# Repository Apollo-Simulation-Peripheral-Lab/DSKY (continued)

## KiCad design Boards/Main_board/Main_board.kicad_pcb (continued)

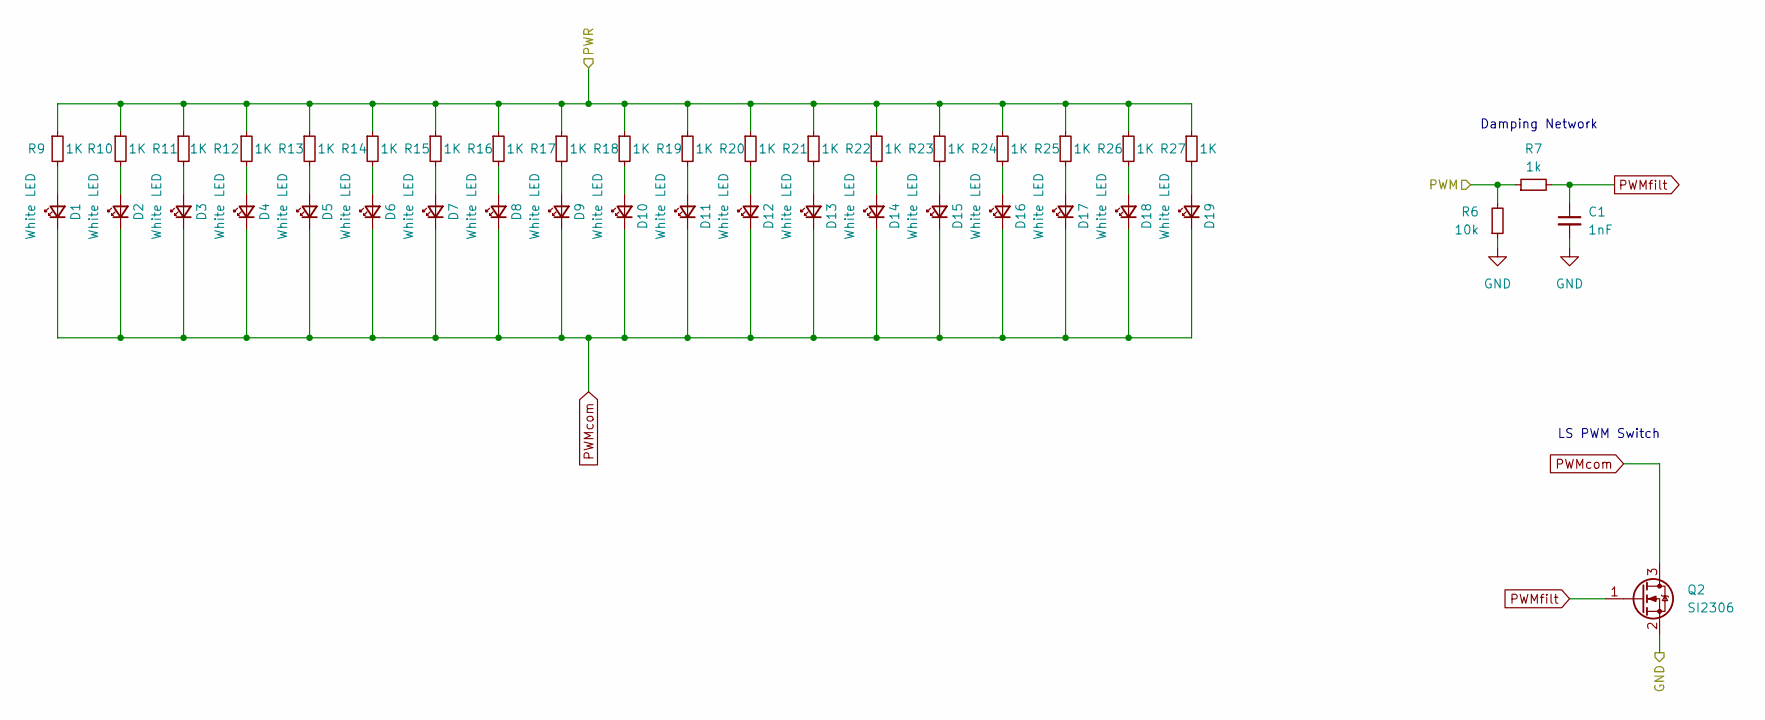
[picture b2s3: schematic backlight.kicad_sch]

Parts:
C1: 1nF; C_1206_3216Metric_Pad1.33x1.80mm_HandSolder; Part Number C1206C102K5RAC
D1, D2, D3, D4, D5, D6, D7, D8, D9, D10, D11, D12, D13, D14, D15, D16, D17, D18, D19: White LED; MX-LED-PolarityMarked
Q2: SI2306; SOT-23-3; Part Number SI2306-TP
R6: 10k; R_1206_3216Metric; Part Number CR1206-FX-1002ELF
R7: 1k; R_1206_3216Metric; Part Number CR1206-FX-1001ELF
R9, R10, R11, R12, R13, R14, R15, R16, R17, R18, R19, R20, R21, R22, R23, R24, R25, R26, R27: 1K; R_1206_3216Metric

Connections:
+5V: R9.1, R10.1, R11.1, R12.1, R13.1, R14.1, R15.1, R16.1, R17.1, R18.1, R19.1, R20.1, R21.1, R22.1, R23.1, R24.1, R25.1, R26.1, R27.1; also elsewhere on the board
GND: C1.2, Q2.2 (S), R6.1; also elsewhere on the board
unnamed: D1.2 (A), R9.2
unnamed: D2.2 (A), R10.2
unnamed: D3.2 (A), R11.2
unnamed: D4.2 (A), R12.2
unnamed: D5.2 (A), R13.2
unnamed: D6.2 (A), R14.2
unnamed: D7.2 (A), R15.2
unnamed: D8.2 (A), R16.2
unnamed: D9.2 (A), R17.2
unnamed: D10.2 (A), R18.2
unnamed: D11.2 (A), R19.2
unnamed: D12.2 (A), R20.2
unnamed: D13.2 (A), R21.2
unnamed: D14.2 (A), R22.2
unnamed: D15.2 (A), R23.2
unnamed: D16.2 (A), R24.2
unnamed: D17.2 (A), R25.2
unnamed: D18.2 (A), R26.2
unnamed: D19.2 (A), R27.2
PWM: R6.2, R7.1; also elsewhere on the board
PWMcom: D1.1 (K), D2.1 (K), D3.1 (K), D4.1 (K), D5.1 (K), D6.1 (K), D7.1 (K), D8.1 (K), D9.1 (K), D10.1 (K), D11.1 (K), D12.1 (K), D13.1 (K), D14.1 (K), D15.1 (K), D16.1 (K), D17.1 (K), D18.1 (K), D19.1 (K), Q2.3 (D)
PWMfilt: C1.1, Q2.1 (G), R7.2

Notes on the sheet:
LS PWM Switch
Damping Network

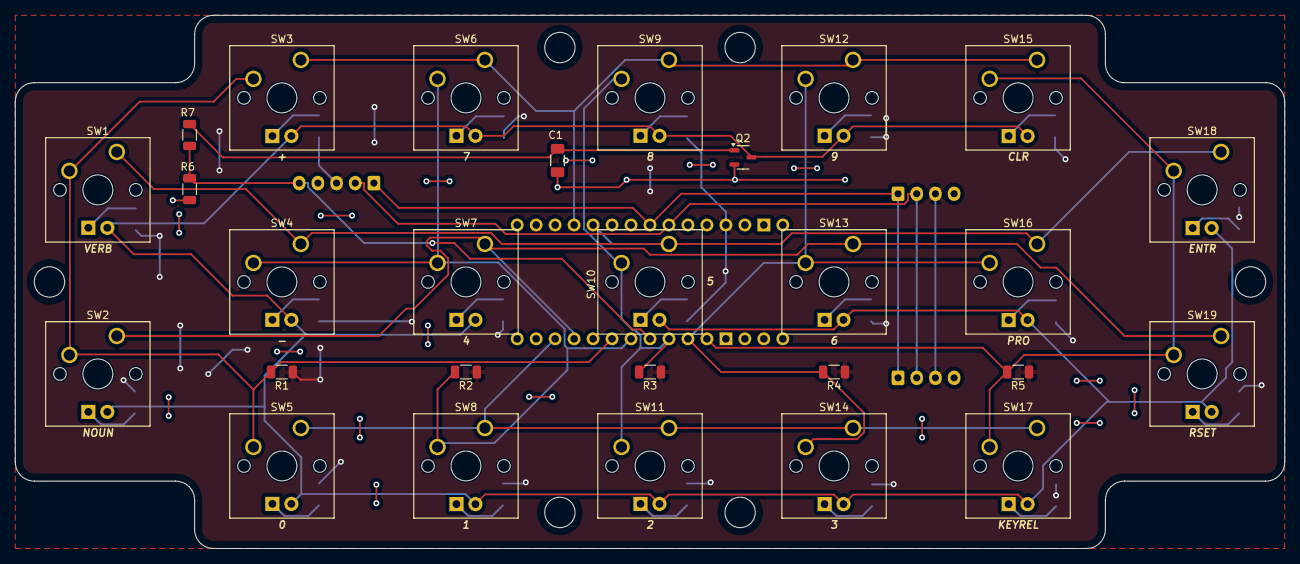
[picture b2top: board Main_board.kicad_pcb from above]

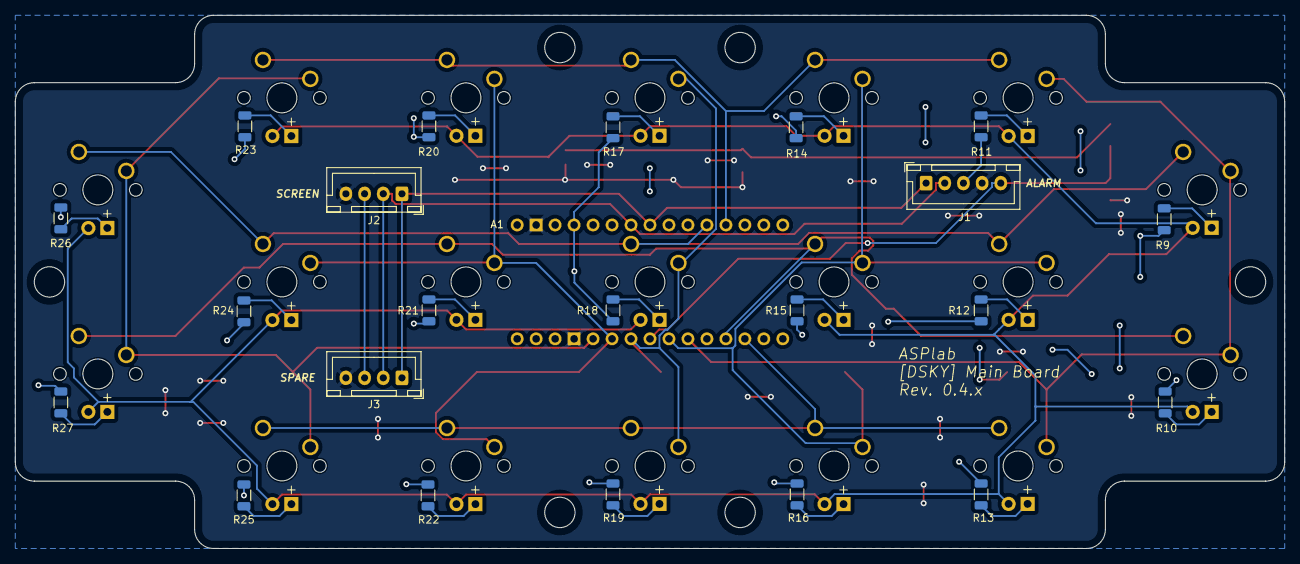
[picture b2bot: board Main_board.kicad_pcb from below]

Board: 2 copper layers, 169.9 x 71.4 mm, 70 parts (23 on the bottom side), 35 nets.

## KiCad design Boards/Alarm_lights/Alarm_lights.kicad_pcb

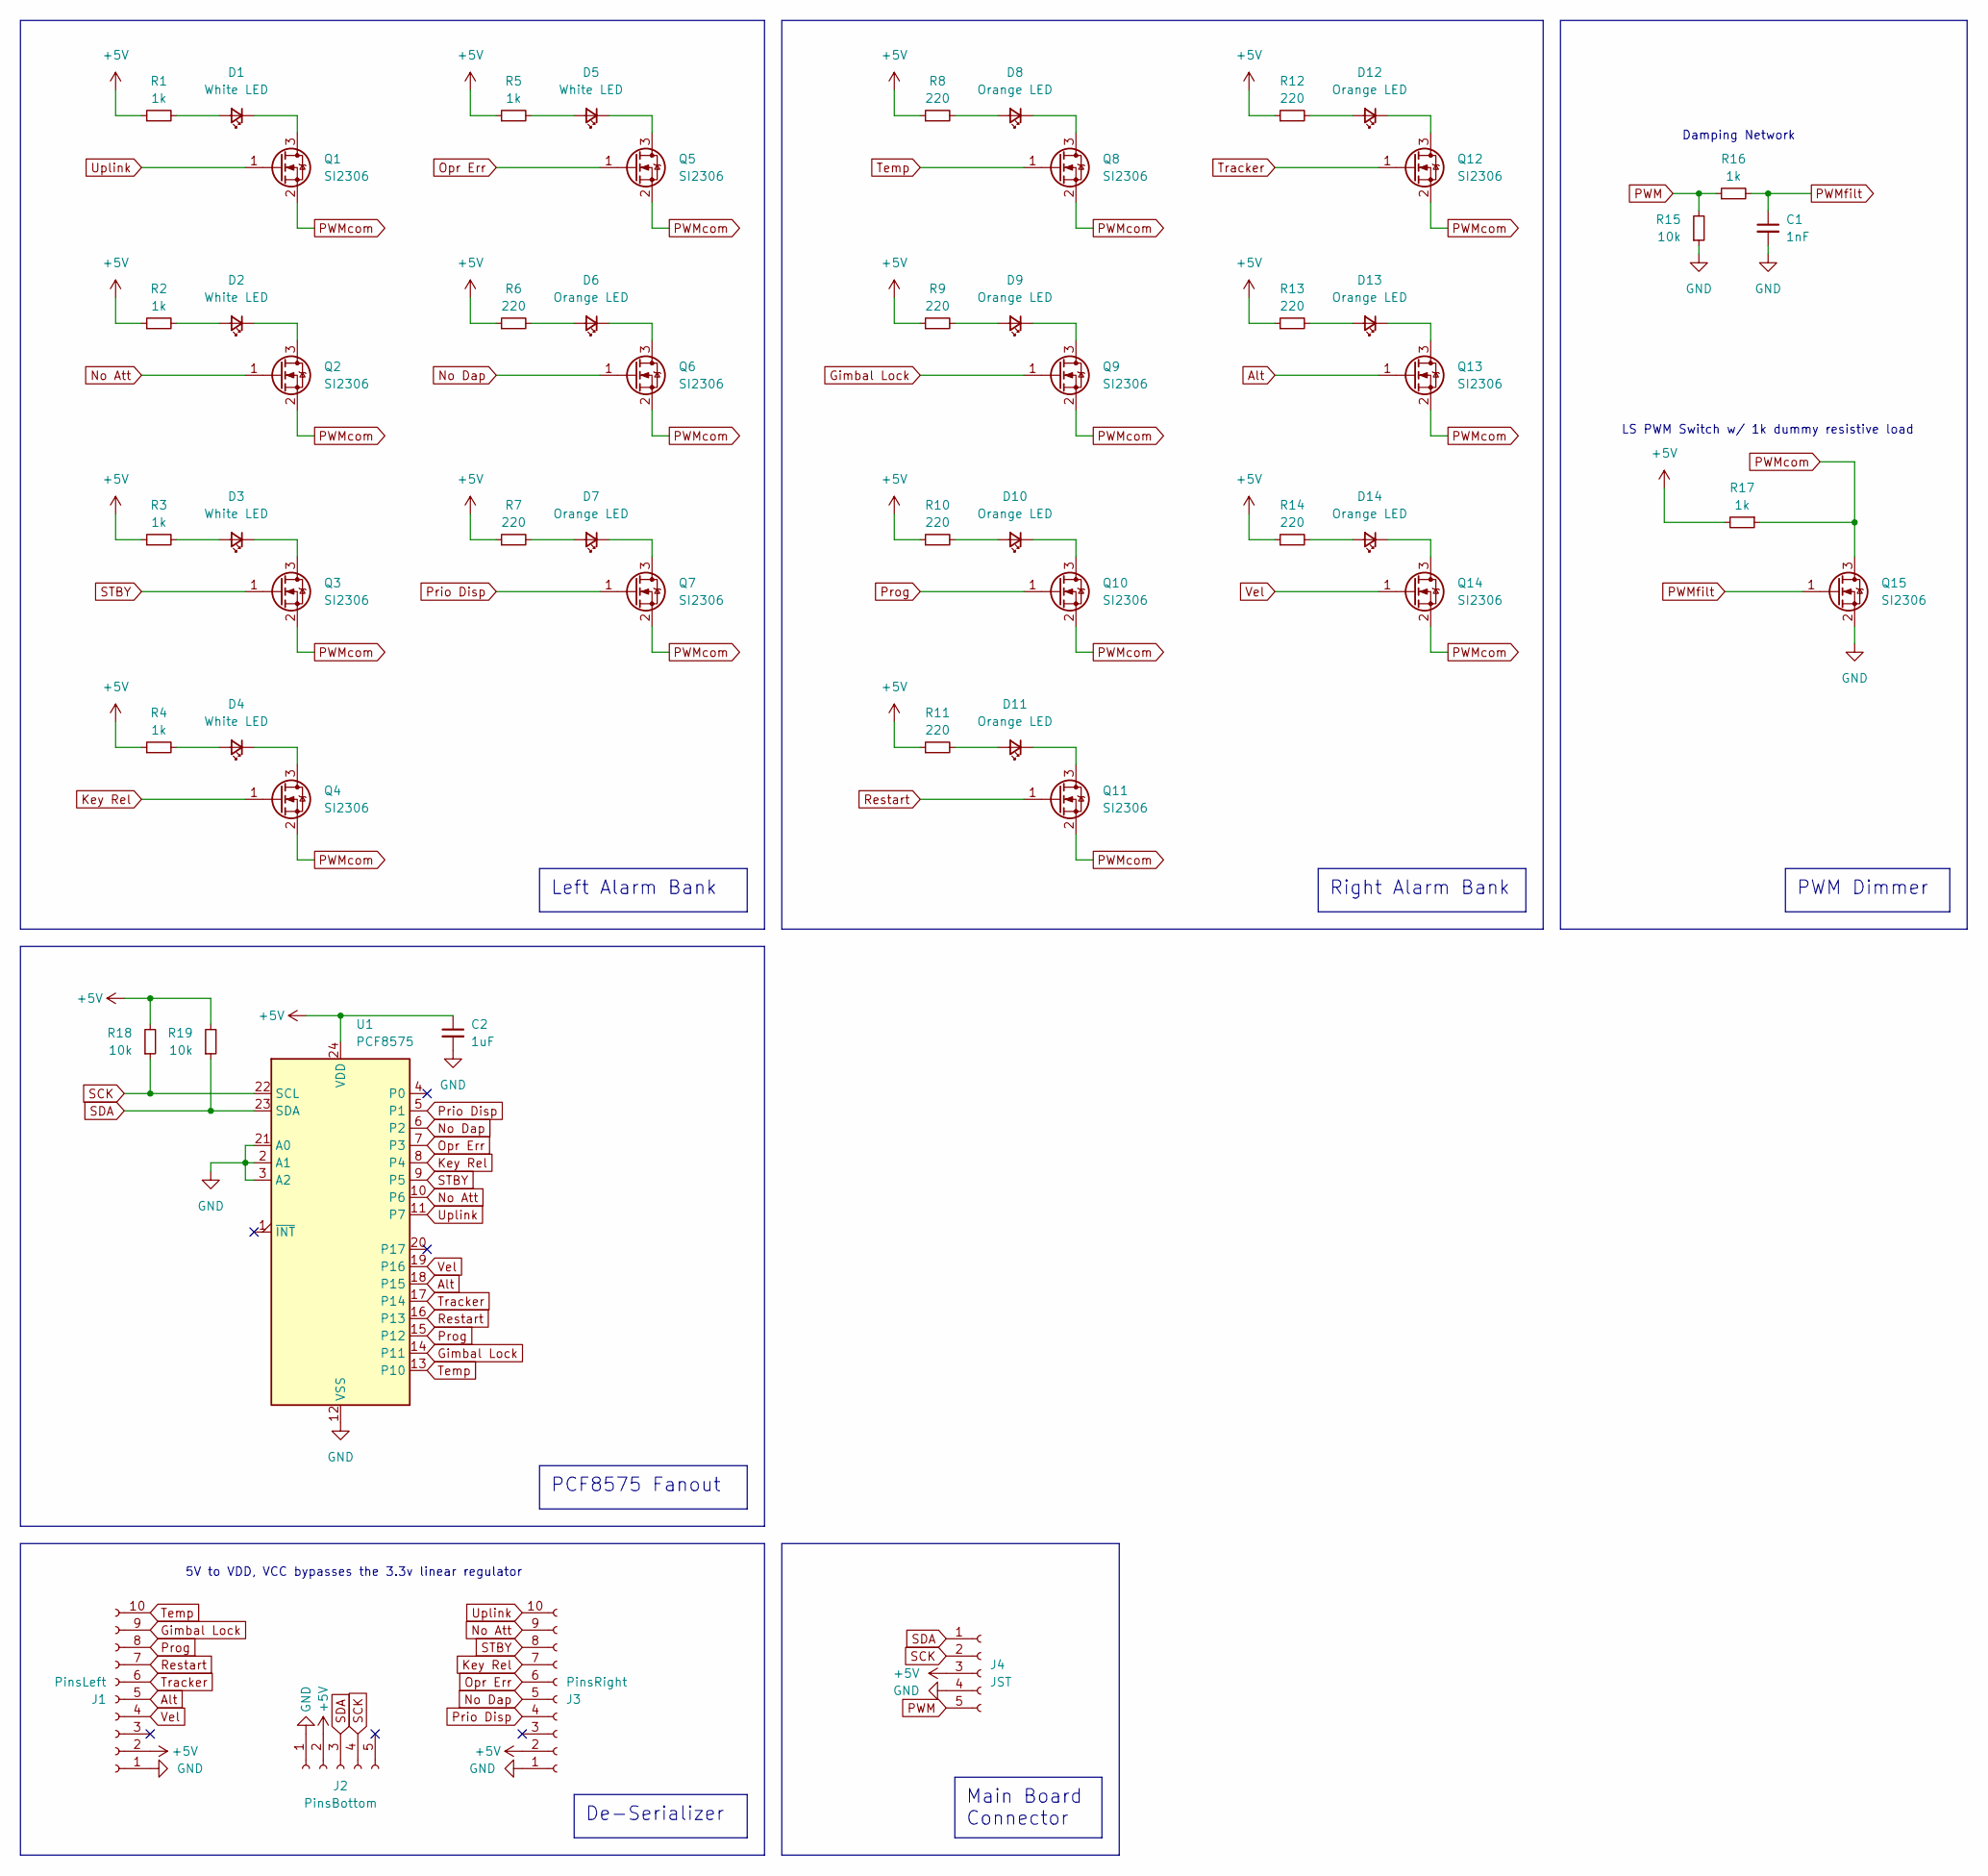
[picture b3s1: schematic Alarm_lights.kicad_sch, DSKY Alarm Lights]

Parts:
C1: 1nF; C_1206_3216Metric_Pad1.33x1.80mm_HandSolder; Part Number C1206C102K5RAC
C2: 1uF; C_1206_3216Metric_Pad1.33x1.80mm_HandSolder; Part Number C1206C105K5RAC
D1, D2, D3, D4, D5: White LED; LED_1206_3216Metric_Pad1.42x1.75mm_HandSolder; Part Number LTW-150TK
D6, D7, D8, D9, D10, D11, D12, D13, D14: Orange LED; LED_1206_3216Metric_Pad1.42x1.75mm_HandSolder; Part Number LTST-C230KFKT
J1: PinsLeft; PinSocket_1x10_P2.54mm_Vertical
J2: PinsBottom; PinSocket_1x05_P2.54mm_Vertical
J3: PinsRight; PinSocket_1x10_P2.54mm_Vertical
J4: JST; JST_XH_B5B-XH-A_1x05_P2.50mm_Vertical
Q1, Q2, Q3, Q4, Q5, Q6, Q7, Q8, Q9, Q10, Q11, Q12, Q13, Q14, Q15: SI2306; SOT-23-3; Part Number SI2306-TP
R1, R2, R3, R4, R5, R16, R17: 1k; R_1206_3216Metric_Pad1.30x1.75mm_HandSolder; Part Number CR1206-FX-1001ELF
R6, R7, R8, R9, R10, R11, R12, R13, R14: 220; R_1206_3216Metric_Pad1.30x1.75mm_HandSolder; Part Number CR1206-FX-2200ELF
R15, R18, R19: 10k; R_1206_3216Metric_Pad1.30x1.75mm_HandSolder; Part Number CR1206-FX-1002ELF
U1: PCF8575; SOIC-24W_7.5x15.4mm_P1.27mm; Part Number PCF8575DWR

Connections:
+5V: C2.1, J1.2, J2.2, J3.2, J4.3, R1.1, R2.1, R3.1, R4.1, R5.1, R6.1, R7.1, R8.1, R9.1, R10.1, R11.1, R12.1, R13.1, R14.1, R17.2, R18.2, R19.2, U1.24 (VDD)
Alt: J1.5, Q13.1 (G), U1.18 (P15)
GND: C1.2, C2.2, J1.1, J2.1, J3.1, J4.4, Q15.2 (S), R15.1, U1.2 (A1), U1.3 (A2), U1.12 (VSS), U1.21 (A0)
Gimbal Lock: J1.9, Q9.1 (G), U1.14 (P11)
Key Rel: J3.7, Q4.1 (G), U1.8 (P4)
unnamed: D1.2 (A), R1.2
unnamed: D1.1 (K), Q1.3 (D)
unnamed: D2.2 (A), R2.2
unnamed: D2.1 (K), Q2.3 (D)
unnamed: D3.2 (A), R3.2
unnamed: D3.1 (K), Q3.3 (D)
unnamed: D4.2 (A), R4.2
unnamed: D4.1 (K), Q4.3 (D)
unnamed: D5.2 (A), R5.2
unnamed: D5.1 (K), Q5.3 (D)
unnamed: D6.2 (A), R6.2
unnamed: D6.1 (K), Q6.3 (D)
unnamed: D7.2 (A), R7.2
unnamed: D7.1 (K), Q7.3 (D)
unnamed: D8.2 (A), R8.2
unnamed: D8.1 (K), Q8.3 (D)
unnamed: D9.2 (A), R9.2
unnamed: D9.1 (K), Q9.3 (D)
unnamed: D10.2 (A), R10.2
unnamed: D10.1 (K), Q10.3 (D)
unnamed: D11.2 (A), R11.2
unnamed: D11.1 (K), Q11.3 (D)
unnamed: D12.2 (A), R12.2
unnamed: D12.1 (K), Q12.3 (D)
unnamed: D13.2 (A), R13.2
unnamed: D13.1 (K), Q13.3 (D)
unnamed: D14.2 (A), R14.2
unnamed: D14.1 (K), Q14.3 (D)
No Att: J3.9, Q2.1 (G), U1.10 (P6)
No Dap: J3.5, Q6.1 (G), U1.6 (P2)
Opr Err: J3.6, Q5.1 (G), U1.7 (P3)
PWM: J4.5, R15.2, R16.1
PWMcom: Q1.2 (S), Q2.2 (S), Q3.2 (S), Q4.2 (S), Q5.2 (S), Q6.2 (S), Q7.2 (S), Q8.2 (S), Q9.2 (S), Q10.2 (S), Q11.2 (S), Q12.2 (S), Q13.2 (S), Q14.2 (S), Q15.3 (D), R17.1
PWMfilt: C1.1, Q15.1 (G), R16.2
Prio Disp: J3.4, Q7.1 (G), U1.5 (P1)
Prog: J1.8, Q10.1 (G), U1.15 (P12)
Restart: J1.7, Q11.1 (G), U1.16 (P13)
SCK: J2.4, J4.2, R18.1, U1.22 (SCL)
SDA: J2.3, J4.1, R19.1, U1.23 (SDA)
STBY: J3.8, Q3.1 (G), U1.9 (P5)
Temp: J1.10, Q8.1 (G), U1.13 (P10)
Tracker: J1.6, Q12.1 (G), U1.17 (P14)
Uplink: J3.10, Q1.1 (G), U1.11 (P7)
Vel: J1.4, Q14.1 (G), U1.19 (P16)

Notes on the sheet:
PCF8575 Fanout
Right Alarm Bank
Main Board Connector
Left Alarm Bank
PWM Dimmer
De-Serializer
Damping Network
LS PWM Switch w/ 1k dummy resistive load
5V to VDD, VCC bypasses the 3.3v linear regulator

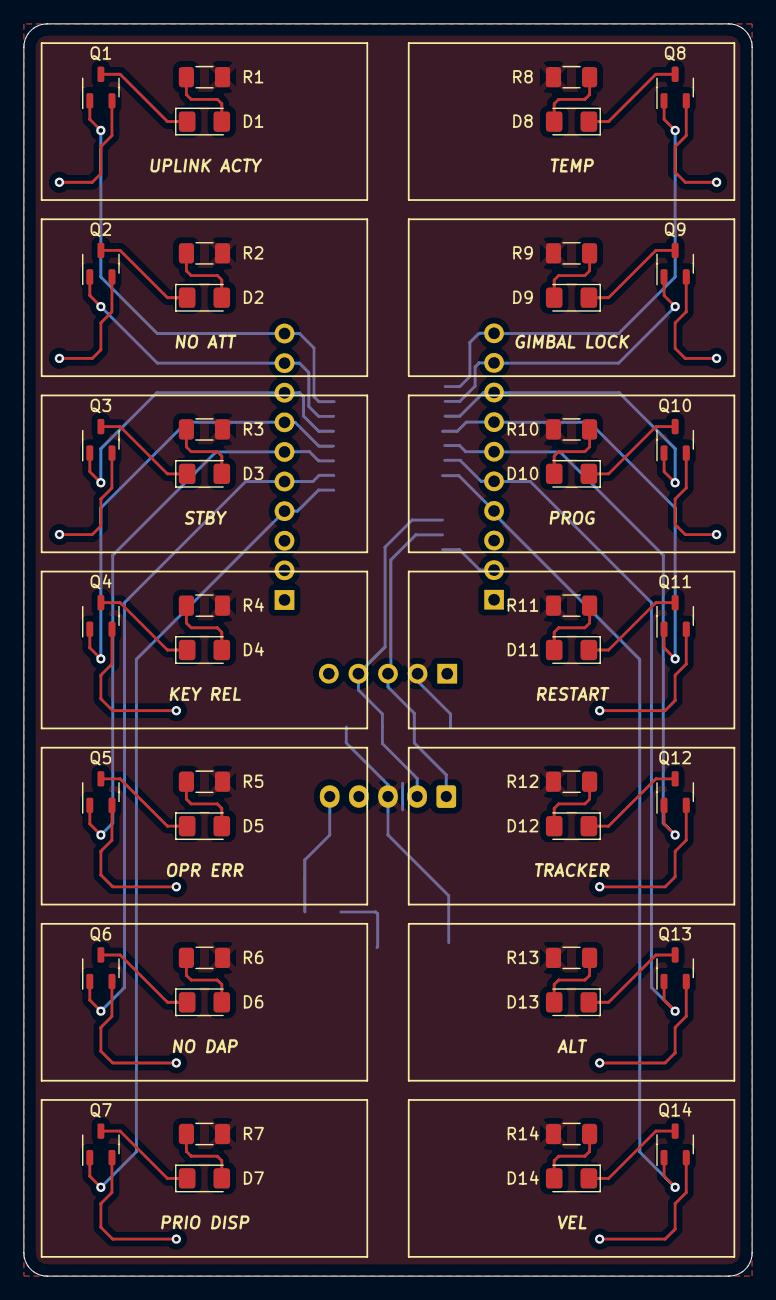
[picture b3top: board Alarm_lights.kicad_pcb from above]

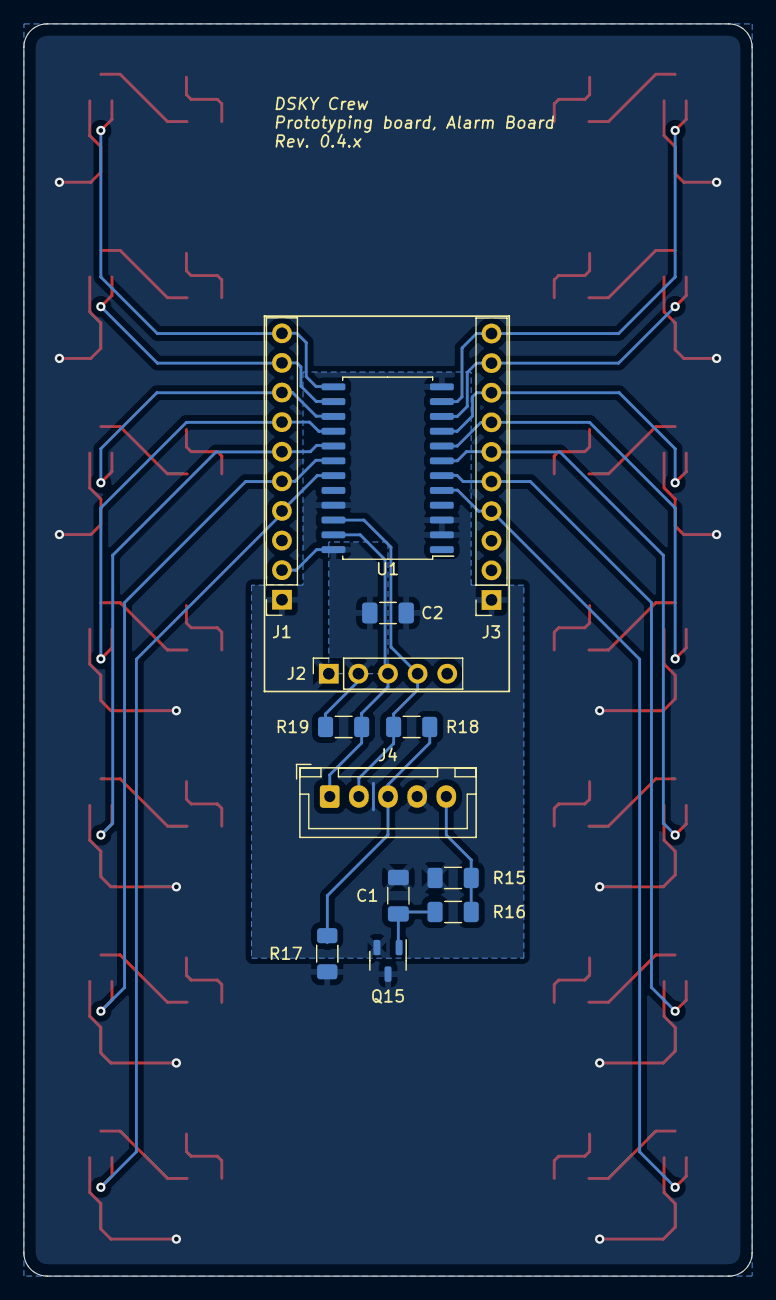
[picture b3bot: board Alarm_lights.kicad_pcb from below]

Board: 2 copper layers, 62.5 x 107.4 mm, 55 parts (13 on the bottom side), 49 nets.

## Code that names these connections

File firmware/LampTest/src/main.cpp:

#include "PCF8575.h"

/* Build defines, per platformio.ini */
#if defined(BUILD_UNO)
#define PWM_PIN 10
#elif defined(BUILD_NANO)
#define PWM_PIN 5
#else
#define PWM_PIN 5
#endif

/* Duty cycle range */
#define DUTY_MIN 1
#define DUTY_MAX 127

/* Delay between test sequence steps */
#define DELAY 1000

/* Total IO pins on the PCF8575 */
#define PCF_PIN_QTY 18

/* Alarm board characteristics */
#define LAMP_QTY 14
#define LAMP_QTY_ORANGE 9
#define LAMP_QTY_WHITE 5

PCF8575 PCF(0x20);

/*           LHC   RHC
UPLINK ACTY    7: :8       TEMP
NO ATT         6: :9       GIMBAL LOCK
STBY           5: :10      PROG
KEY REL        4: :11      RESTART
OPR ERR        3: :12      TRACKER
NO DAP         2: :13      ALT
PRIO DISP      1: :14      VEL
*/

/* IO expander pins of the lamps. */
enum alarmLamp {
  PRIO_DISP = 1,
  NO_DAP = 2,
  OPR_ERR = 3,
  KEY_REL = 4,
  STBY = 5,
  NO_ATT = 6,
  UPLINK_ACTY = 7,
  TEMP = 8,
  GIMBAL_LOCK = 9,
  PROG = 10,
  RESTART = 11,
  TRACKER = 12,
  ALT = 13,
  VEL = 14,
};

/* Map these IO pins to something geographically sensible wrt. the board layout */
const alarmLamp lampMapLeftColumnFirst[14] = {
  UPLINK_ACTY, NO_ATT, STBY, KEY_REL, // lhc
  OPR_ERR, NO_DAP, PRIO_DISP,
  TEMP, GIMBAL_LOCK, PROG, RESTART, // rhc
  TRACKER, ALT, VEL
};

const alarmLamp lampMapRightColumnFirst[14] = {
  TEMP, GIMBAL_LOCK, PROG, RESTART, // rhc
  TRACKER, ALT, VEL,  
  UPLINK_ACTY, NO_ATT, STBY, KEY_REL, // lhc
  OPR_ERR, NO_DAP, PRIO_DISP
};

const alarmLamp lampMapLeftRightDown[14] = {
  UPLINK_ACTY, TEMP, NO_ATT, GIMBAL_LOCK,
  STBY, PROG, KEY_REL, RESTART,
  OPR_ERR, TRACKER, NO_DAP, ALT,
  PRIO_DISP, VEL
};

const alarmLamp lampMapOrange[9] = {
  TEMP, GIMBAL_LOCK, PROG,
  RESTART, TRACKER, NO_DAP,
  ALT, PRIO_DISP, VEL
};

const alarmLamp lampMapWhite[5] = {
  UPLINK_ACTY, NO_ATT, STBY,
  KEY_REL, OPR_ERR
};

/* Function prototypes */
void printHex(uint16_t x);
void toggleAlarm(alarmLamp lamp, uint8_t state, int delayTime);
void toggleAll(uint8_t state);

void testFullScaleBrightness(void);
void testLeftColumnFirst(void);
void testRightColumnFirst(void);
void testLeftRightDown(void);
void testOrangeLamps(void);
void testWhiteLamps(void);

void setup() {
  // configure PWM pin as an output, start I2C and serial buses
  pinMode(PWM_PIN, OUTPUT);
  Serial.begin(MONITOR_SPEED);
  Wire.begin();

  // perform a quick check of the PCF chip, should return 1 and 0xFFFF
  bool connected = PCF.begin();
  Serial.print("PCF8575 Connection: ");
  Serial.println(connected);

  uint16_t x = PCF.read16();
  Serial.print("Read from I2C: ");
  printHex(x);
  
  Serial.println("\nBegin DSKY Alarm Light Test:");


  // get out of hi-z. initialize even the unused PCF pins to LOW state.
  for(uint8_t i = 0; i < PCF_PIN_QTY; i++){
    PCF.write(i, LOW);
  }

}

void loop() {
  // cycle test cases dim, then bright -- over and over
  for(uint8_t i = 0; i < 3; i++)
  {
    switch(i){
      case 0:
        analogWrite(PWM_PIN, DUTY_MIN);
        break;
      case 1:
        analogWrite(PWM_PIN, DUTY_MAX);
        break;
      case 2:
        digitalWrite(PWM_PIN, HIGH);
        break;
    }
  

    Serial.println("Left-right, down");
    testLeftRightDown();

    Serial.println("Left column first");
    testLeftColumnFirst();

    Serial.println("Right column first");
    testRightColumnFirst();

    Serial.println("Orange lamps");
    testOrangeLamps();

    Serial.println("White lamps");
    testWhiteLamps();
    
    Serial.println("Brightness test");  
    testFullScaleBrightness();

    Serial.println();
    toggleAll(0);
    delay(DELAY);
  }
}

/* Toggle all lamps to a particular {state} */
void toggleAll(uint8_t state)
{
  for(uint8_t i = 0; i < LAMP_QTY; i++){
    toggleAlarm(lampMapLeftRightDown[i], state, 20);
  }
}

/* Toggle a single {lamp} to a particular {state} */
void toggleAlarm(alarmLamp lamp, uint8_t state, int delayTime)
{
  for(uint8_t i = 0; i< delayTime / 20; i++){
    PCF.write((uint8_t)lamp, state);
    delay(20);
  }
}

/* Helper -- print something in hex. */
void printHex(uint16_t x)
{
  Serial.print("0x");
  if (x < 0x1000) Serial.print('0');
  if (x < 0x100)  Serial.print('0');
  if (x < 0x10)   Serial.print('0');
  Serial.println(x, HEX);
}

/* Turn on, turn off: Left column then right column.*/
void testLeftColumnFirst(void){
  for(uint8_t i = 0; i < 2; i++)
  {
    for(uint8_t j = 0; j < LAMP_QTY; j++)
    {
      toggleAlarm(lampMapLeftColumnFirst[j], 1 - i, DELAY);
    }
  }
  toggleAll(0);
  return;
}

/* Turn on, turn off: Right column then left column.*/
void testRightColumnFirst(void){
  for(uint8_t i = 0; i < 2; i++)
  {
    for(uint8_t j = 0; j < LAMP_QTY; j++)
    {
      toggleAlarm(lampMapRightColumnFirst[j], 1 - i, DELAY);
    }
  }
  toggleAll(0);
}

/* Turn on, turn off: left then right going down*/
void testLeftRightDown(void)
{
  for(uint8_t i = 0; i < 2; i++)
  {
    for(uint8_t j = 0; j < LAMP_QTY; j++)
    {
      toggleAlarm(lampMapLeftRightDown[j], 1 - i, DELAY);
    }
  }
  toggleAll(0);
}

/* Test all orange lamps. */
void testOrangeLamps(void)
{
  for(uint8_t i = 0; i < 2; i++)
  {
    for(uint8_t j = 0; j < LAMP_QTY_ORANGE; j++)
    {
      toggleAlarm(lampMapOrange[j], 1 - i, DELAY);
    }
  }
  toggleAll(0);
}

/* Test all white lamps. */
void testWhiteLamps(void)
{
  for(uint8_t i = 0; i < 2; i++)
  {
    for(uint8_t j = 0; j < LAMP_QTY_WHITE; j++)
    {
      toggleAlarm(lampMapWhite[j], 1 - i, DELAY);
    }
  }
  toggleAll(0);
}

void testFullScaleBrightness(void)
{
  toggleAll(1);
  uint8_t duty;
  for(uint16_t i = 0 ; i < 510; i++)
  {
    duty = i - 2*(i/256)*(i%255);
    analogWrite(PWM_PIN, duty);
    delay(10);
  }
  analogWrite(PWM_PIN, 0);
}

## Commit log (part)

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2024-03-27 Modularize drawing
2024-03-27 Modularize further
2024-03-27 Eyeballed more realistic green hue
2024-03-28 Failed attempt to render bitmap
2024-03-30 Standalone button matrix test
2024-03-30 decoupling cap now on plane rather than via path
2024-03-30 #42 : Footprint swap, correct minor overlaps
2024-03-30 Add Documentation folder
2024-03-30 Modify mount points for the OrangePi Zero 2W
2024-03-31 Add capability to setup API using DSKY
2024-03-31 Fix merge conflict
2024-03-31 Support aarch64 on API
2024-03-31 Add missing requirements for linux
2024-03-31 Add callback and kill options
2024-03-31 Rebuild API
2024-03-31 Add impl folder to avoid mysterious errors
2024-03-31 #36 Most clearances done
2024-04-03 #36 Update bottom enclosures & finish HDMI LCD housing (print validation pending)
2024-04-03 #36 adjust bottom enclosures to facilitate layout of orangepi related components
2024-04-03 Update mesh files & Readme
2024-04-03 #36 Update body names
2024-04-05 #43 Initial implementation of yaAGC input
2024-04-05 Test yaAGC output code
2024-04-05 Update build
2024-04-05 add debug
2024-04-05 fix variable types
2024-04-05 Improve logs
2024-04-05 test fix
2024-04-06 #36 fix tolerances
2024-04-06 #43 Functional yaAGC output
2024-04-06 #43 yaAGC input finally works
2024-04-06 #43 Implement digit flashing
2024-04-06 #43 Update build
2024-04-06 Add clarification on why NextJS needs downgrading on this architecture
2024-04-08 #43 Fix R1D3 bug
2024-04-08 #43 fix alarms
2024-04-08 #43 improvements in input function
2024-04-08 #43 Finally fix register signs
2024-04-08 #43 allow selection of yaAGC port to allow multiple instances
2024-04-09 #43 Add NoDap and PrioDisp alarms
2024-04-11 Update model and gitignore
2024-04-11 #24 Create UDP listener to test if NASSP output works as expected
2024-04-11 #24 Improve logging
2024-04-12 #24 Add NASSP output
2024-04-12 Update 3d models
2024-04-12 #24 fix dumb mistake
2024-04-12 #24 Improve web rendering of nassp state
2024-04-12 #24 Disable lazy updating of compLight for now
2024-04-14 #24 incorporate alarm values & slight refactor
2024-04-17 Refactor web renderer animation so that api doesn't need to rate-limit state updates
2024-04-17 Clean dist
2024-04-18 (firmware) send pro released event via serial
2024-04-18 (web) send pro release event to api
2024-04-18 Send brightness value to the device
2024-04-27 Implement PRO Release in NASSP integration
2024-05-03 Possibility to scale web-renderer contents
2024-05-03 Update lockfiles
2024-05-03 Reset to default scale
2024-05-10 [web-dsky] Customizable screen type
2024-05-10 Update models
2024-05-10 Fix iPhone13 top margin
2024-05-11 Reorganize 3D Models
2024-05-14 Update 3D Files
2024-05-23 Update fonts
2024-05-28 Receive numerics brightness from nassp and render it on webpage
2024-05-28 Center display on turry's dsky
2024-05-30 Improve rendering of standby state
2024-05-30 Update api build
2024-05-30 Improve display customization a bit
2024-05-30 Fix default display background
2024-05-30 Update models & overflow fix in css
2024-06-01 Add backlight in schematic
2024-06-01 Fix standby handling
2024-06-01 Force nassp dsky to be blank when in standby
2024-06-01 Fix how i forced the EL to be off in standby mode
2024-06-01 Use integral brightness for alarm lights instead of numerics
2024-06-02 Stop using hack to render standby
2024-06-02 Keyboard design refactor to new technique
2024-06-02 Routing of mainboard with backlight
2024-06-02 fix some useless rule check warnings
2024-06-02 Revert "fix some useless rule check warnings"
    This reverts commit 9be92c8e12f23c68fa4d138a37046af0b43376b9.
2024-06-02 Remove dummy load and fix silkscreen collisions
2024-06-02 Generate gerbers for rev4
2024-06-02 Some routing improvements
2024-06-02 GND stitch
2024-06-02 Generate gerbers
2024-06-02 Tag Rev4
2024-06-02 Regenerate broken mesh files
2024-06-03 Make keys better printable
2024-06-05 Add key manufacturing tool & reduce alarms cover height
2024-06-05 Finetune keys & update fusion project
2024-06-07 Middle enclosure improvements
2024-06-07 Adjust keyboard plate clearance
2024-06-10 Sturdier cover in HDMI variant
2024-06-11 Fix alarm cover thickness
2024-06-12 Update Readme.md
    Added Discord Link to Readme.md
2024-06-14 Update Assembly file
2024-06-16 Add resin sliced files for keys
2024-06-16 firmware - Fix self-test mode
2024-06-16 firmware - Fix self-test mode while keeping support for bad io chips
2024-06-18 Lower keyboard and fix self test
2024-06-18 Better adjust content to LCD display
2024-06-22 Add OrangePi image file to ignored
2024-06-22 Update resin sliced files
2024-06-22 Prepare boards to be ordered with assembly
2024-06-23 Tolerance adjustments
2024-06-23 remove 3mf meshes
2024-06-23 Improve hdmi board housing
2024-06-24 Modify Mainboard to enable support for PCB type switches
2024-06-26 Small 3d tweaks
2024-06-27 Convert more models to stl
2024-06-29 Convert more meshes to .stl
2024-06-29 Use new Reentry UDP api for input instead of nut-js
2024-06-29 convert some meshes to stl
2024-06-29 Improve reentry implementation of udp
2024-06-29 First implementation of homeassistant mode (it still doesn't do anything)
2024-06-29 build api
2024-06-30 Refactor initial agc nodejs implementation
2024-06-30 Implement vnFlashing in reentry
2024-06-30 Tie numerics to led brightness for nassp while integrals is missing
2024-06-30 Fix register3 position
2024-06-30 test adding another verb
2024-06-30 refactor custom AGC
2024-06-30 Add a bit more logic to my AGC
2024-06-30 Implement v22 and v23 too
2024-06-30 Control edge cases
2024-06-30 Add N36
2024-07-02 First implementation of orangepi init script
2024-07-02 update orangepi script
2024-07-02 try to start yaagc within the api
2024-07-02 fix path and build
2024-07-02 Try to fix exec
2024-07-02 try to fix yaagc start
2024-07-02 lint orangepi init
2024-07-02 improve start menu
2024-07-02 fix J-mission in yaAGC mode
2024-07-03 Add shutdown handler option & kill yaAGC when api exits
2024-07-05 Better organization of 3d files
2024-07-06 convert mesh to stl
2024-07-06 Add alarms to DSKY renderer & improve oled mode handling
2024-07-06 Fix yaAGC buffer limit & nextjs build
2024-07-06 ability to override display type in url
2024-07-07 Re-stitch and clean up redundant tracks. Correct some port directions.
2024-07-07 Remove annoying robotjs dependency for windows users
2024-07-08 Raster alarm texts
2024-07-08 Initial implementation of nassp handler
2024-07-08 Nassp cloud manager is working
2024-07-08 Fix websocket input
2024-07-08 Fix nassp handler
2024-07-08 disable freeze detection
2024-07-09 improvements in nassp handler
2024-07-09 adjust timing
2024-07-09 Fix V35
2024-07-09 Prevent V35 reset
2024-07-10 Remove redundant GND tracks in place of vias. Continue rerouting & condensing. Make PWMCom 20mil
2024-07-10 restart every hour
2024-07-10 Initial layout of single board alternative
2024-07-10 some progress on the arduino boilerplate
2024-07-10 Single board nearly ready to order
2024-07-10 Fixes on single board
2024-07-10 More visual improvements
2024-07-10 fix cherry 3d models in footprints
2024-07-10 Silkscreen fixes & PCBWay assembly files
2024-07-10 Connect AVCC to VCC
2024-07-10 Better via placement
2024-07-10 Update white leds to comply with JLC's request
2024-07-10 Try to fix nassp standby mode & remove unused map
2024-07-10 Undo unnecessary fix
2024-07-10 Fix alarm opacity in web renderer
2024-07-11 Re-add needed map for dsky keyboard handling
2024-07-11 Improve V35 detection
2024-07-11 [nassp] Change input approach & add integralBrightness to output
2024-07-11 Fix vulnerabilities
2024-07-11 Unify all NASSP dsky output in a single socket
2024-07-12 [web-dsky] Style fixes
2024-07-12 get anun out of nassp if available
2024-07-12 Add missing key models
2024-07-12 Improve handling of brightness values, localized to DSKY context
2024-07-12 Webpage style fixes
2024-07-13 Implement rate-limiting in state updates
2024-07-13 Undo css hack
2024-07-13 Update default address for wss bridge
2024-07-13 Improve css logic
2024-07-13 Improve dimming calculation in firmware
2024-07-14 Hold PRO for 3 seconds to confirm shutdown and API exit
2024-07-14 Improve rate limiting logic
2024-07-14 Fine tune limiting rate
2024-07-15 Report connected clients to all websocket clients
2024-07-15 Show client list in webpage
2024-07-15 Improve client list handling
2024-07-15 inform websocket users of all clients with their same IP
2024-07-15 Fix agent handling
2024-07-17 Fix iphone mode styling
2024-07-17 Fix keyboard position in iOS
2024-07-17 Fix keyboard buttons
2024-07-17 keyboard positioning adjustments
2024-07-17 virtual keyboard hidden by default
2024-07-17 Fix PRO on virtual keyboard
2024-07-17 Update models & firmware to acomodate single board
2024-07-17 Raster alarms texts & increase printing efficiency
2024-07-17 small adjustments in splitter
2024-07-19 vectorize keyboard text
2024-07-20 Add 'cron' script for orangepi memory cleanup
2024-07-21 Ability to upload from PlatformIO via ICSP
2024-07-21 [HA] V16 improvements
2024-07-21 Implement brightness controls for reentry
2024-07-21 Fix reentry brightness normalization
2024-07-21 Ensure normalized value stays within range
2024-07-23 Clean up 3d project
2024-07-23 Cleanup repo a bit
2024-07-26 Add options to program
2024-07-27 Add hot-reload development mode
2024-07-27 Improve compound verbs & other stuff
2024-07-27 Update bundle
2024-07-27 Ability to read AC state
2024-07-27 Show temperature and humidity decimals
2024-07-27 [HA] Implement V35 and mock AC state update
2024-08-03 Fix crash due to experimental HomeAssistant mode
2024-08-03 Fix another issue caused by HA
2024-08-07 Prepare models for laser engraved keys
2024-10-29 mesh improvements
2024-10-29 bom updates
2024-10-31 Organize meshes
2024-11-09 Start RGB LED + hotswap socket redesign of single board
2024-11-12 Add usb ports and separate power sources. Pending fitting test.
2024-11-15 Board and 3d models update
2024-11-16 Plane layout
2024-11-16 Initial autoroute
2024-11-17 Small routing improvements and prepare for JLC order
2024-11-17 JLC adjustments
2024-11-18 Autoroute and change rgb led footprint
2024-11-18 Fix led footprint & autoroute
2024-11-19 Some stitching but led arrangement is suboptimal
2024-11-19 Optimize led positions
2024-11-19 Autoroute and a bit of stitching
2024-11-19 more stitching
2024-11-19 some symmetry
2024-11-20 Relayout of LED section
2024-11-20 Better GND stitching & silkscreen fixes
2024-11-20 Fix DRC
2024-11-20 Update pads on sk6812
2024-11-20 reposition some vias
2024-11-20 Adjust JLC positioning
2024-12-04 Initial neopixel implementation
2024-12-04 Fix stupid routing mistake
2024-12-06 Implement dsky mode using neopixels. also some cool effects
2024-12-06 Customizable baudrate for bad atmegas
2024-12-06 Clean project a bit
2024-12-07 Update some models
2024-12-07 Fix wrong cleanup of boards
2024-12-07 Updated gerber files
2024-12-07 Lighting improvements
2024-12-07 Add extra params for orangepi autostart
2024-12-07 Fix extra params
2024-12-07 Fix random brightness
2024-12-07 Fix tabs
2024-12-07 handle serial errors
2024-12-07 try to fix bridge
2024-12-07 Reduce power consumption on boot to help orangepi boot successfully
2024-12-10 Revert to 250k baudrate
2024-12-10 default 250k baudrate on api
2024-12-10 use 250k baudrate in firmware
2024-12-11 Change baudrate back to 9600 to ensure integrity
2024-12-12 Use RESTART as Atmega power up indicator instead of UPLINK ACTY
2024-12-23 Update tolerances
2024-12-23 Add Keyboard plate variant
2025-01-01 Add painting tools & improve tolerances on 1-part SLA keys
2025-01-07 push tolerances to the limit
2025-01-09 Adjust ENTR and VERB tolerances
2025-01-10 save resin
2025-02-11 Adjust baudrate to 9600 to match latest api defaults
2025-02-11 Adjust baudrate in platformio
2025-02-11 Bring recent compatible developments into rev4's firmware & board state
2025-02-16 Add yaagc spawn parameter
2025-04-03 Try to ignore excess bytes
2025-11-30 Update KiCad project files with new settings and enhancements
2025-11-30 Fix Alarms document
2025-12-02 add new key holder for shipping
2026-05-14 update model
2026-06-06 fdm tweaks & replica enclosure export
